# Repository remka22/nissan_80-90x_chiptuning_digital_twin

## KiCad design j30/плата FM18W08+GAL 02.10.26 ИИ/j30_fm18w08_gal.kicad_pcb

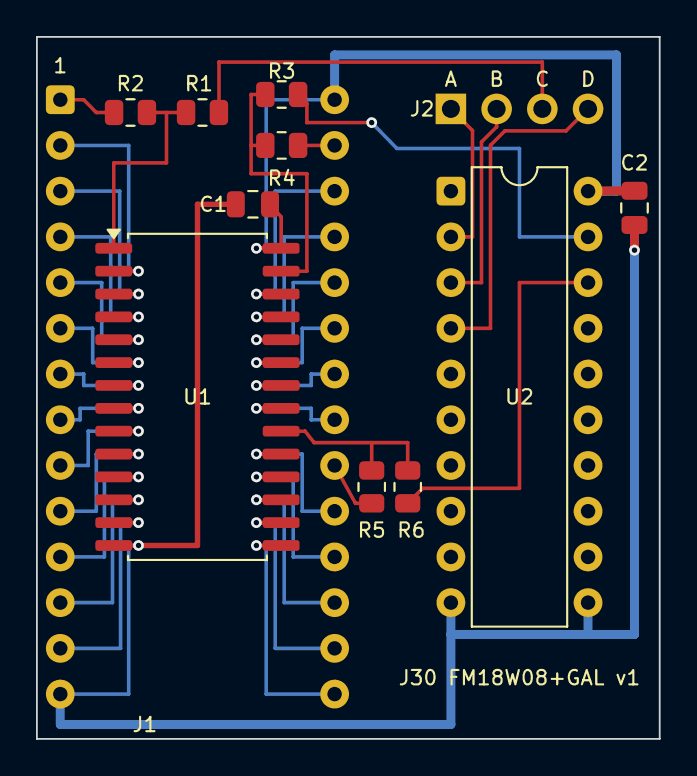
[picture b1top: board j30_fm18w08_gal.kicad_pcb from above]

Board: 2 copper layers, 34.6 x 39.0 mm, 12 parts (0 on the bottom side), 37 nets.

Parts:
C1, C2: 100n; C_0805_2012Metric
J1: ШТЫРИ В ПАНЕЛЬ ЭБУ; DIP-28_W15.24mm
J2: ЭБУ A B C D; PinHeader_1x04_P2.54mm_Vertical
R1, R2, R3, R4, R5, R6: 0R; R_0805_2012Metric
U1: FM18W08-SG; SOIC-28W_7.5x17.9mm_P1.27mm
U2: GAL16V8B; DIP-20_W7.62mm

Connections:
/CE: J1.20, R5.2
/OE: J1.22, U1.22
A0: J1.10, U1.10
A1: J1.9, U1.9
A2: J1.8, U1.8
A3: J1.7, U1.7
A4: J1.6, U1.6
A5: J1.5, U1.5
A6: J1.4, U1.4
A7: J1.3, U1.3
A8: J1.25, U1.25
A9: J1.24, U1.24
A10: J1.21, U1.21
A11: J1.23, U1.23
A12: J1.2, U1.2
A13: J1.26, U1.26
A14: J2.3, R1.2
A15: J2.2, U2.3
D0: J1.11, U1.11
D1: J1.12, U1.12
D2: J1.13, U1.13
D3: J1.15, U1.15
D4: J1.16, U1.16
D5: J1.17, U1.17
D6: J1.18, U1.18
D7: J1.19, U1.19
E: J2.1, U2.2
FM_/CE: R5.1, R6.1, U1.20
FM_/WE: R3.1, R4.1, U1.27
FM_A14: R1.1, R2.1, U1.1
GAL_/CE: R6.2, U2.18
GAL_/WE: R3.2, U2.19
GND: C1.1, C2.2, J1.14, U1.14, U2.10, U2.11
PIN1_PRG: J1.1, R2.2
PIN27_PRG: J1.27, R4.2
R/W: J2.4, U2.4
VCC: C1.2, C2.1, J1.28, U1.28, U2.20

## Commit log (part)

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2026-06-25 Инициализация да бл
